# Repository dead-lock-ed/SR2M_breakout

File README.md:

# SR2M_breakout
Breakout board for a Schrank / TE Connectivity SR2M Form A + B force guided relay

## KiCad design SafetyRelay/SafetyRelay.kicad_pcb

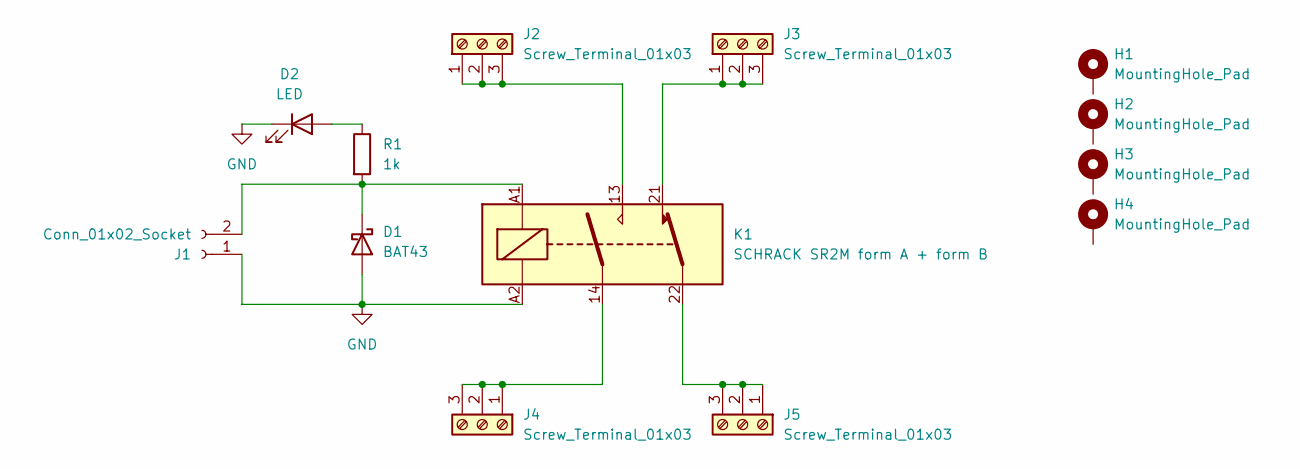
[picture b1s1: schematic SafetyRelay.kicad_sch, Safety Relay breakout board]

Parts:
D1: BAT43; D_DO-35_SOD27_P7.62mm_Horizontal
D2: LED; LED_D3.0mm
H1, H2, H3, H4: MountingHole_Pad; MountingHole_3.2mm_M3_ISO7380_Pad
J1: Conn_01x02_Socket; JST_XH_B2B-XH-A_1x02_P2.50mm_Vertical
J2, J3, J4, J5: Screw_Terminal_01x03; TerminalBlock_RND_205-00046_1x03_P5.00mm_Horizontal
K1: SCHRACK SR2M form A + form B; Relay_Schrack-SR2M-FormA+B
R1: 1k; R_Axial_DIN0204_L3.6mm_D1.6mm_P5.08mm_Horizontal

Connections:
GND: D1.2 (A), D2.1 (K), J1.1, K1.A2
unnamed: D1.1 (K), J1.2, K1.A1, R1.2
unnamed: D2.2 (A), R1.1
unnamed: J2.1, J2.2, J2.3, K1.13
unnamed: J3.1, J3.2, J3.3, K1.21
unnamed: J4.1, J4.2, J4.3, K1.14
unnamed: J5.1, J5.2, J5.3, K1.22

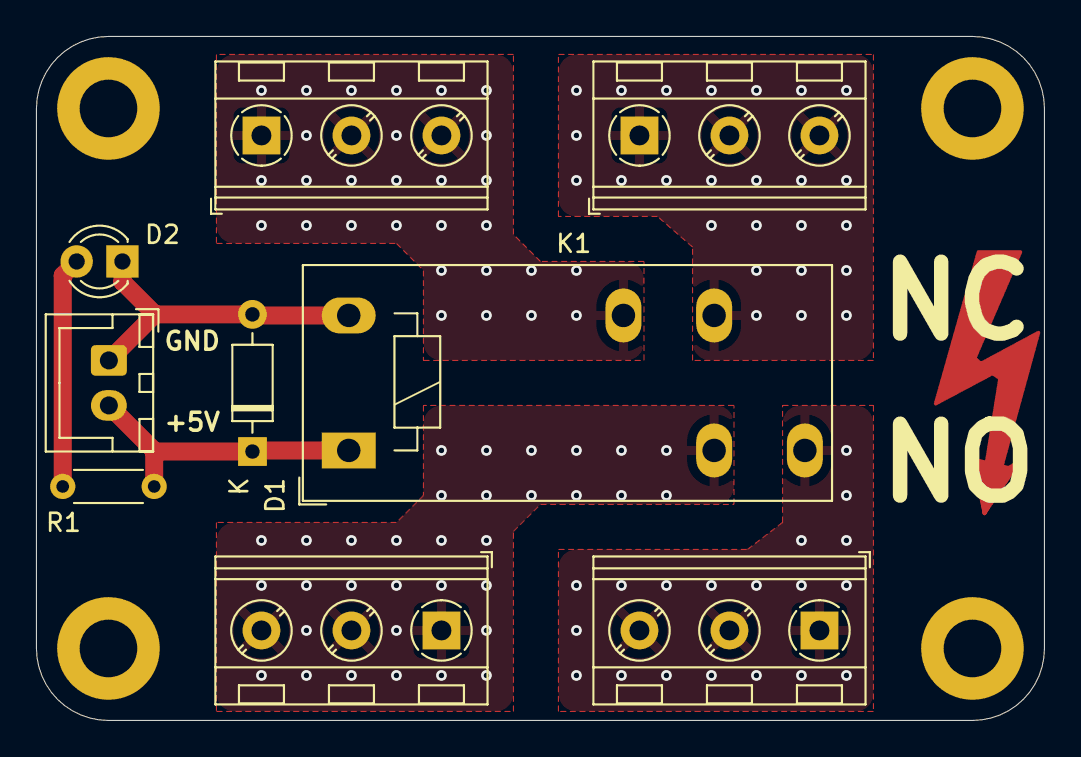
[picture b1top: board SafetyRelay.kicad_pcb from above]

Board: 2 copper layers, 56.0 x 38.0 mm, 13 parts (0 on the bottom side), 7 nets.

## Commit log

2025-07-06 Create LICENSE
2025-07-07 Added KiCAD files
2025-07-07 Added GRB prodution files
2025-07-07 Added BOM for Mouser
